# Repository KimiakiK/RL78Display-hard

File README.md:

# RL78Display-hard

## パーツリスト
- [RL78/G13 R5F100LLAFA 512KB/32KB](https://www.marutsu.co.jp/pc/i/226841/)
- [TFT 1.3inch 240x240](https://akizukidenshi.com/catalog/g/gP-15695/)
- [RTC IC RX8900CE](https://akizukidenshi.com/catalog/g/gI-13320/)
- タッチセンサIC TTP223
- [コネクタ FFC Bottom 12極 0.5mm](https://www.marutsu.co.jp/pc/i/15778034/)
- [表面実装圧電ブザー](https://akizukidenshi.com/catalog/g/gP-14238/)
- [水晶発振子 32.768kHz](https://akizukidenshi.com/catalog/g/gP-07195/)
- [レギュレータ 3.3V 500mA SOT89-5 NJM2884U1-33](https://akizukidenshi.com/catalog/g/gI-10673/)
- [レギュレータ 3.0V 100mA SOT-23-5 NJM2864F03](https://akizukidenshi.com/catalog/g/gI-16314/)
- [マイクロUSBコネクタ](https://akizukidenshi.com/catalog/g/gC-11183/)
- [ミニUSBコネクタ](https://akizukidenshi.com/catalog/g/gC-05690/)
- [NchパワーMOSFET SOT-23](https://akizukidenshi.com/catalog/g/gI-14653/)
- [青色チップLED 1608](https://akizukidenshi.com/catalog/g/gI-11881)
- [白色チップLED 1608](https://akizukidenshi.com/catalog/g/gI-11882)
- [コンデンサ 0.22F 3.3V](https://akizukidenshi.com/catalog/g/gP-00240/)
- [チップコンデンサ 2.2uF 1608](https://akizukidenshi.com/catalog/g/gP-16077/)
- [チップコンデンサ 1uF 1608](https://akizukidenshi.com/catalog/g/gP-14526/)
- [チップコンデンサ 0.1uF 1608](https://akizukidenshi.com/catalog/g/gP-13374/)
- [チップコンデンサ 330pF 1608](https://akizukidenshi.com/catalog/g/gP-05584/)
- [チップコンデンサ 10pF 1005](https://akizukidenshi.com/catalog/g/gP-13400/)
- [フェライトビーズBLM18PPG600SN 1608](https://akizukidenshi.com/catalog/g/gP-04442/)
- [リセッタブルヒューズ 9V 200mA 1608](https://akizukidenshi.com/catalog/g/gP-14311/)

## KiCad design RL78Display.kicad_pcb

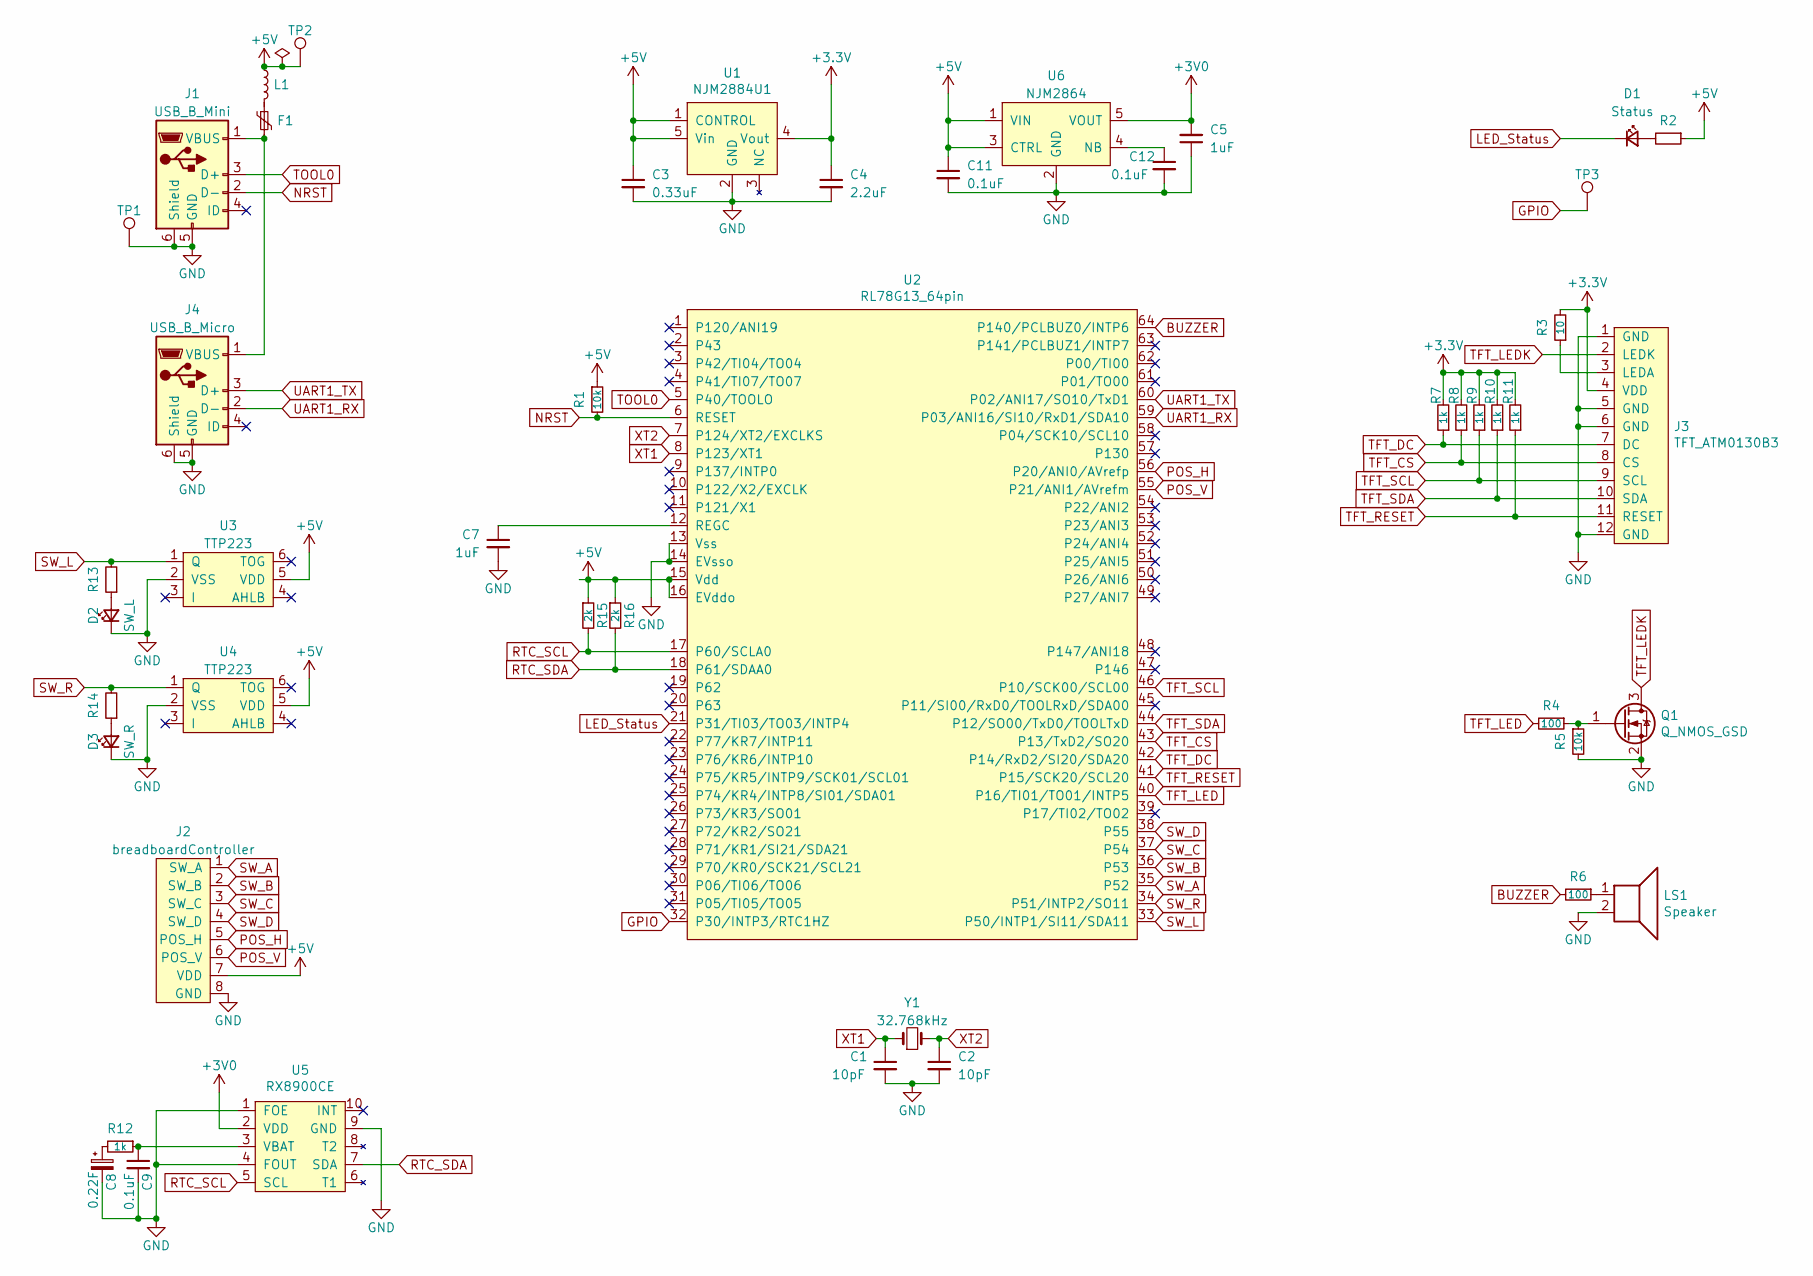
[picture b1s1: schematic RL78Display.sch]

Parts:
C1, C2: 10pF; 1005Metric
C3: 0.33uF; 1608Metric
C4: 2.2uF; 1608Metric
C5, C7: 1uF; 1608Metric
C8: 0.22F; DCK-3R3E224-E
C9, C11, C12: 0.1uF; 1608Metric
D1: Status; 1608Metric
D2: SW_L; 1608Metric
D3: SW_R; 1608Metric
F1: Polyfuse_Small; 1608Metric
J1: USB_B_Mini; UX60SC-MB-5ST
J2: breadboardController; PinHeader_1x08_P2.54mm_Vertical
J3: TFT_ATM0130B3; Hirose_FH12-12S-0.5SH_1x12-1MP_P0.50mm_Horizontal
J4: USB_B_Micro; ZX62-B-5PA
L1: L_Small; 1608Metric
LS1: Speaker; PKMCS0909E4000
Q1: Q_NMOS_GSD; SOT-23
R1, R5: 10k; 1608Metric
R2, R13, R14: R; 1608Metric
R3: 10; 1608Metric
R4, R6: 100; 1608Metric
R7, R8, R9, R10, R11, R12: 1k; 1608Metric
R15, R16: 2k; 1608Metric
TP1, TP2, TP3: TestPoint; TestPoint_THTPad_D1.4mm_Drill0.8mm
U1: NJM2884U1; SOT-89-5
U2: RL78G13_64pin; LQFP-64-12x12nn-P0.65mm_FusionPCB
U3, U4: TTP223; SOT-23-6
U5: RX8900CE
U6: NJM2864; SOT-23-5
Y1: 32.768kHz; Crystal_SMD_3215-2Pin

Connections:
+3V0: C5.2, U5.2 (VDD), U6.5 (VOUT)
+3V3: C4.1, J3.4 (VDD), R3.2, R7.2, R8.2, R9.2, R10.2, R11.2, U1.4 (Vout)
+5V: C3.1, C11.1, J2.7 (VDD), L1.1, R1.1, R2.1, R15.1, R16.1, TP2.1, U1.1 (CONTROL), U1.5 (Vin), U2.15 (Vdd), U2.16 (EVddo), U3.5 (VDD), U4.5 (VDD), U6.1 (VIN), U6.3 (CTRL)
BUZZER: R6.2, U2.64 (P140/PCLBUZ0/INTP6)
GND: C1.2, C2.2, C3.2, C4.2, C5.1, C7.2, C8.2, C9.2, C11.2, C12.2, D2.1 (K), D3.1 (K), J1.5 (GND), J1.6 (Shield), J2.8 (GND), J3.1 (GND), J3.5 (GND), J3.6 (GND), J3.12 (GND), J4.5 (GND), J4.6 (Shield), LS1.2, Q1.2 (S), R5.2, TP1.1, U1.2 (GND), U2.13 (Vss), U2.14 (EVsso), U3.2 (VSS), U4.2 (VSS), U5.1 (FOE), U5.4 (FOUT), U5.9 (GND), U6.2 (GND)
GPIO: TP3.1, U2.32 (P30/INTP3/RTC1HZ)
LED_Status: D1.1 (K), U2.21 (P31/TI03/TO03/INTP4)
NRST: J1.2 (D-), R1.2, U2.6 (RESET)
unnamed: C7.1, U2.12 (REGC)
unnamed: C8.1, R12.2
unnamed: C9.1, R12.1, U5.3 (VBAT)
unnamed: C12.1, U6.4 (NB)
unnamed: D1.2 (A), R2.2
unnamed: D2.2 (A), R13.1
unnamed: D3.2 (A), R14.1
unnamed: F1.1, L1.2
unnamed: F1.2, J1.1 (VBUS), J4.1 (VBUS)
unnamed: J3.3 (LEDA), R3.1
unnamed: LS1.1, R6.1
unnamed: Q1.1 (G), R4.1, R5.1
POS_H: J2.5 (POS_H), U2.56 (P20/ANI0/AVrefp)
POS_V: J2.6 (POS_V), U2.55 (P21/ANI1/AVrefm)
RTC_SCL: R15.2, U2.17 (P60/SCLA0), U5.5 (SCL)
RTC_SDA: R16.2, U2.18 (P61/SDAA0), U5.7 (SDA)
SW_A: J2.1 (SW_A), U2.35 (P52)
SW_B: J2.2 (SW_B), U2.36 (P53)
SW_C: J2.3 (SW_C), U2.37 (P54)
SW_D: J2.4 (SW_D), U2.38 (P55)
SW_L: R13.2, U2.33 (P50/INTP1/SI11/SDA11), U3.1 (Q)
SW_R: R14.2, U2.34 (P51/INTP2/SO11), U4.1 (Q)
TFT_CS: J3.8 (CS), R8.1, U2.43 (P13/TxD2/SO20)
TFT_DC: J3.7 (DC), R7.1, U2.42 (P14/RxD2/SI20/SDA20)
TFT_LED: R4.2, U2.40 (P16/TI01/TO01/INTP5)
TFT_LEDK: J3.2 (LEDK), Q1.3 (D)
TFT_RESET: J3.11 (RESET), R11.1, U2.41 (P15/SCK20/SCL20)
TFT_SCL: J3.9 (SCL), R9.1, U2.46 (P10/SCK00/SCL00)
TFT_SDA: J3.10 (SDA), R10.1, U2.44 (P12/SO00/TxD0/TOOLTxD)
TOOL0: J1.3 (D+), U2.5 (P40/TOOLO)
UART1_RX: J4.2 (D-), U2.59 (P03/ANI16/SI10/RxD1/SDA10)
UART1_TX: J4.3 (D+), U2.60 (P02/ANI17/SO10/TxD1)
XT1: C1.1, U2.8 (P123/XT1), Y1.1
XT2: C2.1, U2.7 (P124/XT2/EXCLKS), Y1.2

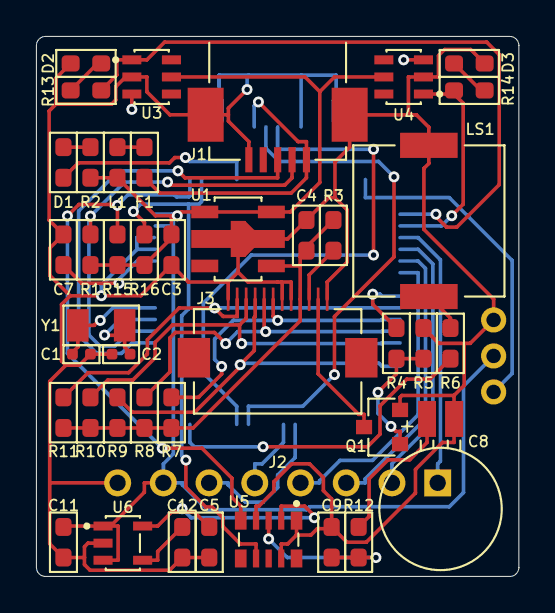
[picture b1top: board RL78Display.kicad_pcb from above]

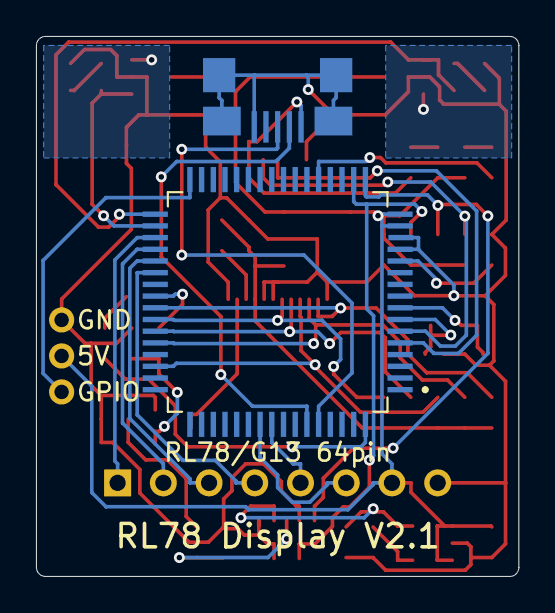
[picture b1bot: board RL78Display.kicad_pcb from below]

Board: 2 copper layers, 26.8 x 30.0 mm, 47 parts (5 on the bottom side), 42 nets.

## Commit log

2021-04-11 基板 V1.0
2021-05-27 基板 V1.1
2021-06-20 基板 V2.0
2021-07-10 基板 V2.1
2021-10-06 パーツリスト追加
